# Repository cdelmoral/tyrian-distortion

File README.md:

# Tyrian Distortion Guitar Pedal

This project contains the kicad files for the Tyrian distortion guitar pedal, designed by
[PedalPCB](https://www.pedalpcb.com/product/tyriandistortion/) (thank you!).

## Requirements

In order to open the project you will need to have [kicad](https://www.kicad.org/) installed
in your computer.

## Bill of Materials

TODO

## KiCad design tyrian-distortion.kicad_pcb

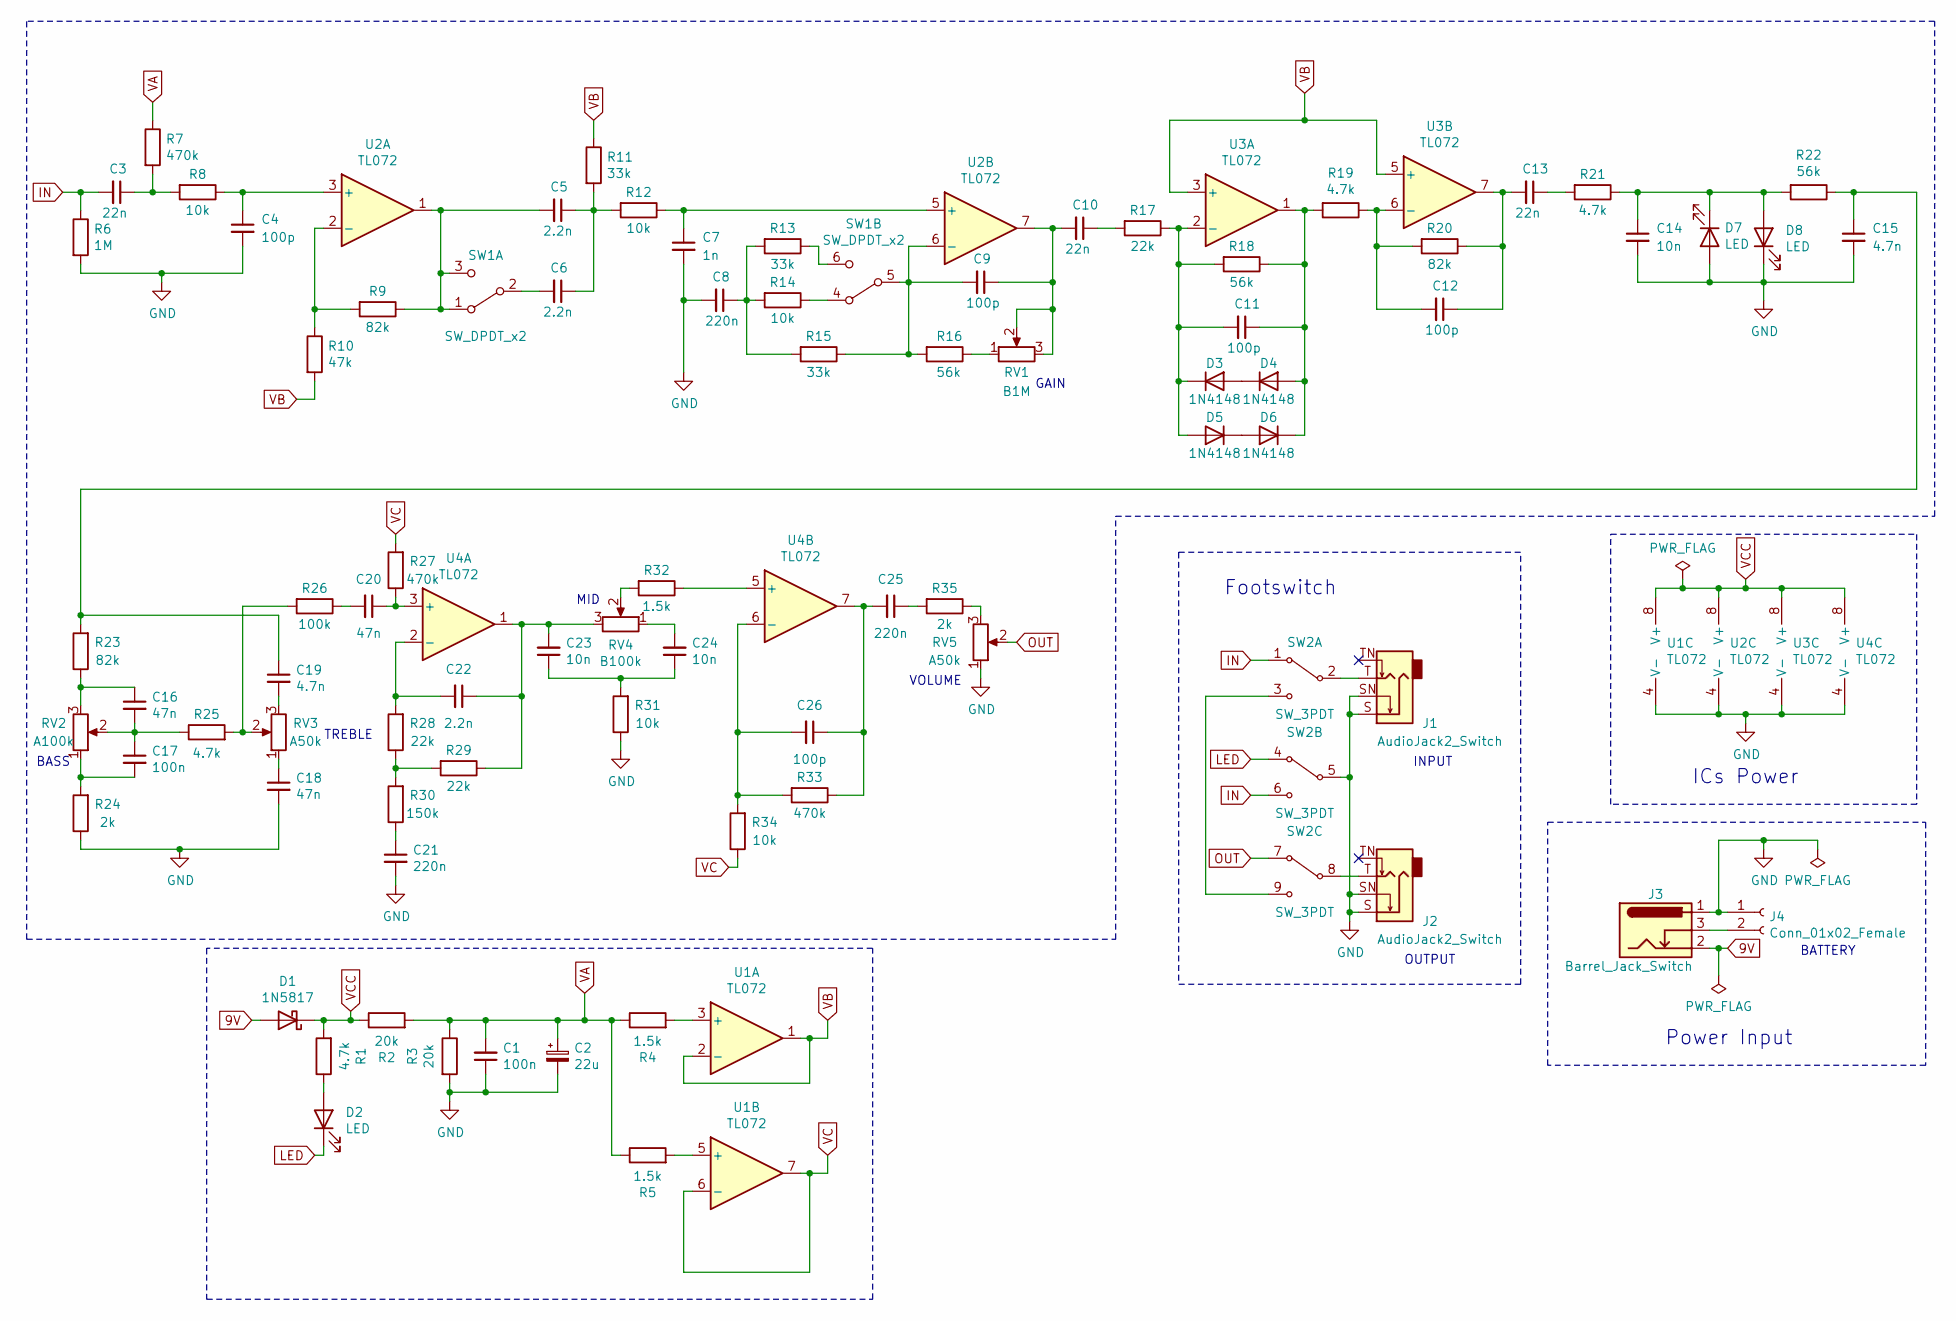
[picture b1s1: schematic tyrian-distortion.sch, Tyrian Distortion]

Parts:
C1, C17: 100n; C_Disc_D5.0mm_W2.5mm_P2.50mm
C2: 22u; CP_Radial_D5.0mm_P2.00mm
C3, C10, C13: 22n; C_Disc_D3.4mm_W2.1mm_P2.50mm
C4, C9, C11, C12, C26: 100p; C_Disc_D3.4mm_W2.1mm_P2.50mm
C5, C6, C22: 2.2n; C_Disc_D3.4mm_W2.1mm_P2.50mm
C7: 1n; C_Disc_D3.4mm_W2.1mm_P2.50mm
C8, C21, C25: 220n; C_Disc_D8.0mm_W2.5mm_P5.00mm
C14, C23, C24: 10n; C_Disc_D3.4mm_W2.1mm_P2.50mm
C15, C19: 4.7n; C_Disc_D3.4mm_W2.1mm_P2.50mm
C16, C18, C20: 47n; C_Disc_D3.4mm_W2.1mm_P2.50mm
D1: 1N5817; D_DO-41_SOD81_P10.16mm_Horizontal
D2: LED; LED_D5.0mm
D3, D4, D5, D6: 1N4148; D_DO-35_SOD27_P7.62mm_Horizontal
D7, D8: LED; LED_D3.0mm
J1, J2: AudioJack2_Switch; Jack_6.35mm_Neutrik_NMJ4HCD2_Horizontal
J3: Barrel_Jack_Switch; BarrelJack_Wuerth_6941xx301002
J4: Conn_01x02_Female; TerminalBlock_2pin_2.54mm
R1, R19, R21, R25: 4.7k; R_Axial_DIN0207_L6.3mm_D2.5mm_P10.16mm_Horizontal
R2, R3: 20k; R_Axial_DIN0207_L6.3mm_D2.5mm_P10.16mm_Horizontal
R4, R5, R32: 1.5k; R_Axial_DIN0207_L6.3mm_D2.5mm_P10.16mm_Horizontal
R6: 1M; R_Axial_DIN0207_L6.3mm_D2.5mm_P10.16mm_Horizontal
R7, R27, R33: 470k; R_Axial_DIN0207_L6.3mm_D2.5mm_P10.16mm_Horizontal
R8, R12, R14, R31, R34: 10k; R_Axial_DIN0207_L6.3mm_D2.5mm_P10.16mm_Horizontal
R9, R20, R23: 82k; R_Axial_DIN0207_L6.3mm_D2.5mm_P10.16mm_Horizontal
R10: 47k; R_Axial_DIN0207_L6.3mm_D2.5mm_P10.16mm_Horizontal
R11, R13, R15: 33k; R_Axial_DIN0207_L6.3mm_D2.5mm_P10.16mm_Horizontal
R16, R18, R22: 56k; R_Axial_DIN0207_L6.3mm_D2.5mm_P10.16mm_Horizontal
R17, R28, R29: 22k; R_Axial_DIN0207_L6.3mm_D2.5mm_P10.16mm_Horizontal
R24, R35: 2k; R_Axial_DIN0207_L6.3mm_D2.5mm_P10.16mm_Horizontal
R26: 100k; R_Axial_DIN0207_L6.3mm_D2.5mm_P10.16mm_Horizontal
R30: 150k; R_Axial_DIN0207_L6.3mm_D2.5mm_P10.16mm_Horizontal
RV1: B1M; Tayda_Potentiometer
RV2: A100k; Tayda_Potentiometer
RV3, RV5: A50k; Tayda_Potentiometer
RV4: B100k; Tayda_Potentiometer
SW1: SW_DPDT_x2; DPDT_Toggle_Switch
SW2: SW_3PDT; 3PDT_Toggle_Switch
U1, U2, U3, U4: TL072; DIP-8_W7.62mm

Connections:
9V: D1.2 (A), J3.2
GND: C1.1, C2.2, C4.2, C7.2, C8.2, C14.2, C15.2, C18.2, C21.2, D7.2 (A), D8.1 (K), J1.S, J1.SN, J2.S, J2.SN, J3.1, J4.1, R3.2, R6.2, R24.1, R31.1, RV5.1, SW2.5, U1.4 (V-), U2.4 (V-), U3.4 (V-), U4.4 (V-)
IN: C3.2, R6.1, SW2.1, SW2.6
LED: D2.1 (K), SW2.4
unnamed: C3.1, R7.2, R8.2
unnamed: C4.1, R8.1, U2.3 (+)
unnamed: C5.1, C6.1, R11.2, R12.2
unnamed: C5.2, R9.1, SW1.1 (A), SW1.3 (C), U2.1
unnamed: C6.2, SW1.2 (B)
unnamed: C7.1, R12.1, U2.5 (+)
unnamed: C8.1, R13.2, R14.2, R15.2
unnamed: C9.2, R15.1, R16.2, SW1.5 (B), U2.6 (-)
unnamed: C10.1, R17.2
unnamed: C9.1, C10.2, RV1.2, RV1.3, U2.7
unnamed: C11.1, D4.2 (A), D6.1 (K), R18.1, R19.2, U3.1
unnamed: C11.2, D3.1 (K), D5.2 (A), R17.1, R18.2, U3.2 (-)
unnamed: C12.1, C13.2, R20.1, U3.7
unnamed: C12.2, R19.1, R20.2, U3.6 (-)
unnamed: C13.1, R21.2
unnamed: C14.1, D7.1 (K), D8.2 (A), R21.1, R22.2
unnamed: C15.1, C19.1, R22.1, R23.2
unnamed: C16.1, R23.1, RV2.3
unnamed: C16.2, C17.1, R25.1, RV2.2
unnamed: C17.2, R24.2, RV2.1
unnamed: C18.1, RV3.1
unnamed: C19.2, RV3.3
unnamed: C20.1, R27.1, U4.3 (+)
unnamed: C20.2, R26.1
unnamed: C21.1, R30.1
unnamed: C22.1, C23.2, R29.1, RV4.3, U4.1
unnamed: C22.2, R28.2, U4.2 (-)
unnamed: C23.1, C24.1, R31.2
unnamed: C24.2, RV4.1
unnamed: C25.1, R35.2
unnamed: C25.2, C26.1, R33.1, U4.7
unnamed: C26.2, R33.2, R34.2, U4.6 (-)
unnamed: D2.2 (A), R1.1
unnamed: D3.2 (A), D4.1 (K)
unnamed: D5.1 (K), D6.2 (A)
unnamed: J1.T, SW2.2
unnamed: J2.T, SW2.8
unnamed: J3.3, J4.2
unnamed: R4.2, U1.3 (+)
unnamed: R5.2, U1.5 (+)
unnamed: R9.2, R10.1, U2.2 (-)
unnamed: R13.1, SW1.6 (C)
unnamed: R14.1, SW1.4 (A)
unnamed: R16.1, RV1.1
unnamed: R25.2, R26.2, RV3.2
unnamed: R28.1, R29.2, R30.2
unnamed: R32.1, U4.5 (+)
unnamed: R32.2, RV4.2
unnamed: R35.1, RV5.3
unnamed: SW2.3, SW2.9
OUT: RV5.2, SW2.7
VA: C1.2, C2.1, R2.2, R3.1, R4.1, R5.1, R7.1
VB: R10.2, R11.1, U1.1, U1.2 (-), U3.3 (+), U3.5 (+)
VC: R27.2, R34.1, U1.6 (-), U1.7
VCC: D1.1 (K), R1.2, R2.1, U1.8 (V+), U2.8 (V+), U3.8 (V+), U4.8 (V+)

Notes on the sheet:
Footswitch
ICs Power
Power Input
GAIN
BASS
TREBLE
MID
VOLUME
INPUT
OUTPUT
BATTERY

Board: 2 copper layers, 84 parts (0 on the bottom side), 59 nets, no tracks yet.

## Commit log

2022-05-01 feat: Create schematic
    - Adds completed schematic
    - Adds 3PDT component
2022-05-01 docs: Add README.md
2022-05-02 feat: Create footprint associations
    - Adds custom footprints for DPDT and 3PDT
    - Minor fixes to schema
